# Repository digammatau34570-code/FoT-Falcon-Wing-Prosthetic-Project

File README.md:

# FoT Falcon Wing Prosthetic Project

An Arduino-controlled, 3D-printed prosthetic arm and hand assembly designed and built for the FoT Falcon Wing Prosthetic Project and the Falcon Olympics.

## Repository Contents
* `FalconWingProstheticCode.ino` - Main Arduino microcontroller firmware for servo/actuator/button/myoware-sensor control.
* `Falcon Wing Microcontroller CAD/` - Arduino Nano CAD Model and KiCad PCB/schematic files.
* `Falcon Wing Prosthetic Arm CAD/` - Lower Arm CAD Model for wearing purposes.
* `Falcon Wing Prosthetic Hand CAD/` - Hand CAD for the actual hand used for holding and grabbing items.
* `Falcon Wing Prosthetic Upper Arm CAD/` - Upper Arm CAD for connecting the arm and the hand and for housing the servo.
* `Falcon Wing Prosthetic Project Slice.3mf` — Pre-configured 3D printer slicer project file.

## Hardware & Electronics
* **Microcontroller:** Arduino Nano/Uno
* **Actuators:** Tower Pro Micro Servo 9g sg90
* **Sensors / Inputs:** MyoWare 2.0 Muscle Sensor(EMG), MyoWare 2.0 Arduino Shield, SunFounder Button v2.0
* **Power Supply:** One 9V Battery for Uno, 4 Duracell AA Batteries for Nano(with 1 1N400x Series Diode).

## 3D Printing & Slicer Settings
* **File:** `Falcon Wing Prosthetic Project Slice.3mf`, `Falcon Wing Microcontroller CAD/`, `Falcon Wing Prosthetic Arm CAD/`, `Falcon Wing Prosthetic Hand CAD/`, `Falcon Wing Prosthetic Upper Arm CAD/`
* **Recommended Material:** PLA
* **Infill & Layer Height:** 15% infill, 0.2 mm layer height
* **Supports:** No supports included for print.

## Getting Started
1. **3D Print Parts:** Open `Falcon Wing Prosthetic Project Slice.3mf` in your slicer and print the structural components.
2. **Wire Electronics:** Follow wiring diagrams to connect the microcontroller, sensors, and servos.
3. **Upload Firmware:** Open `FalconWingProstheticCode.ino` in the Arduino IDE, select your board and COM port, and click **Upload**.

## Team & Contributors
* `@digammatau34570-code`
* `@shrikaisme`

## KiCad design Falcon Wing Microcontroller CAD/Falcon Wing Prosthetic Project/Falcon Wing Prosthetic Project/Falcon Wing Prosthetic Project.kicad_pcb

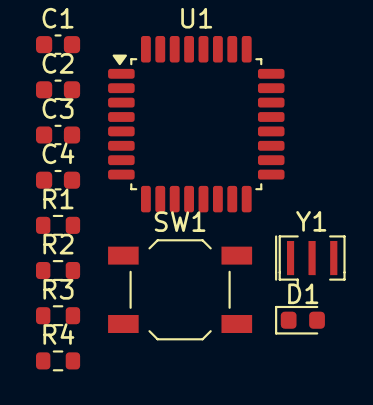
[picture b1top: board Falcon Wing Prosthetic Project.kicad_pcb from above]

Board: 2 copper layers, 12 parts (0 on the bottom side), 11 nets, no tracks yet.

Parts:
C1, C2: 1u; C_0603_1608Metric
C3: 100n; C_0603_1608Metric
C4: 4u7_16V; C_0603_1608Metric
D1: Yellow; LED_0603_1608Metric
R1, R2, R3, R4: 1k; R_0603_1608Metric
SW1: SW_Push; SW_SPST_TL3342
U1: ATmega328P-A; TQFP-32_7x7mm_P0.8mm
Y1: 16MHz; Resonator_SMD_Murata_CSTxExxV-3Pin_3.0x1.1mm

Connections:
+5V: C1.1, C2.1, C4.1, R1.1, U1.4 (VCC), U1.6 (VCC), U1.18 (AVCC)
/AREF: C3.1, U1.20 (AREF)
/D0/RX: R2.1, U1.30 (PD0)
/D1/TX: R3.1, U1.31 (PD1)
/D13/SCK: R4.1, U1.17 (PB5)
/RESET: R1.2, SW1.1, U1.29 (~RESET/PC6)
/XTAL1: U1.7 (XTAL1/PB6), Y1.3
/XTAL2: U1.8 (XTAL2/PB7), Y1.1
GND: C1.2, C2.2, C3.2, C4.2, D1.1 (K), SW1.2, Y1.2
unnamed: D1.2 (A), R4.2
unnamed: U1.3 (GND), U1.5 (GND), U1.21 (GND)
